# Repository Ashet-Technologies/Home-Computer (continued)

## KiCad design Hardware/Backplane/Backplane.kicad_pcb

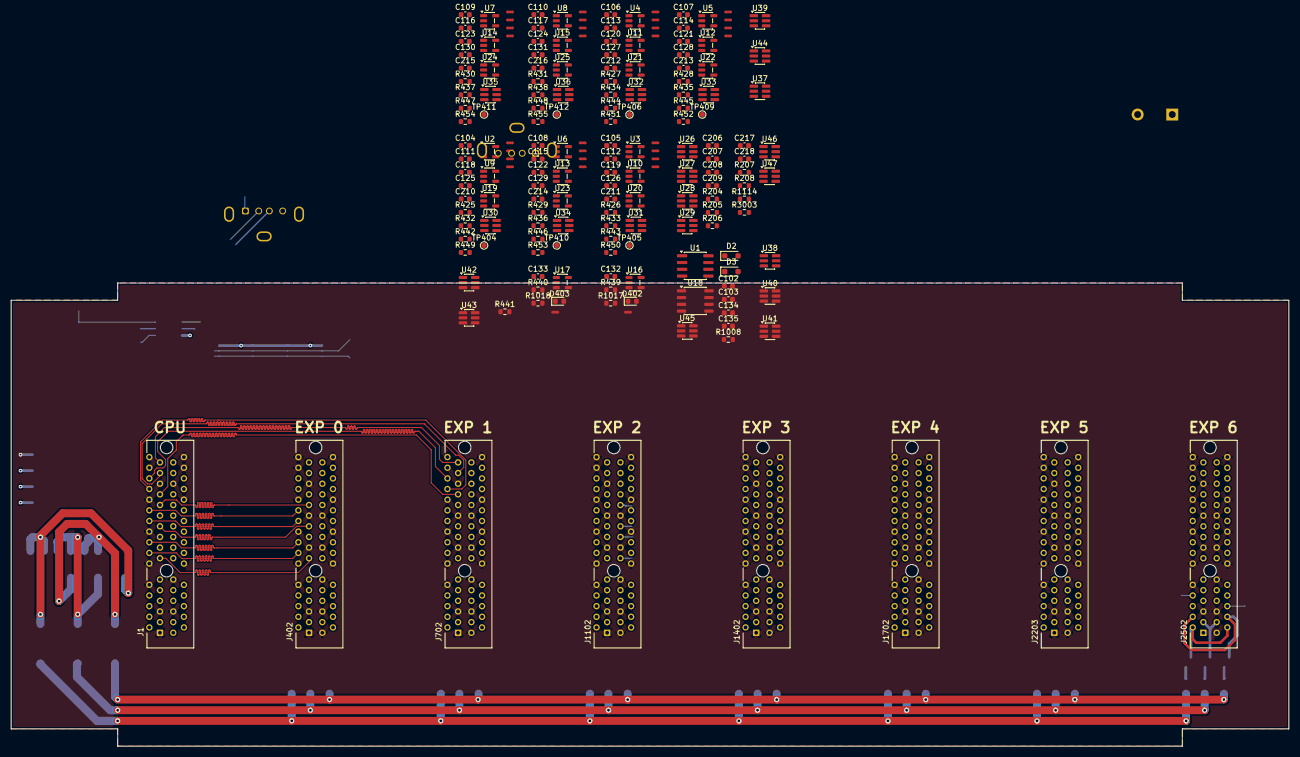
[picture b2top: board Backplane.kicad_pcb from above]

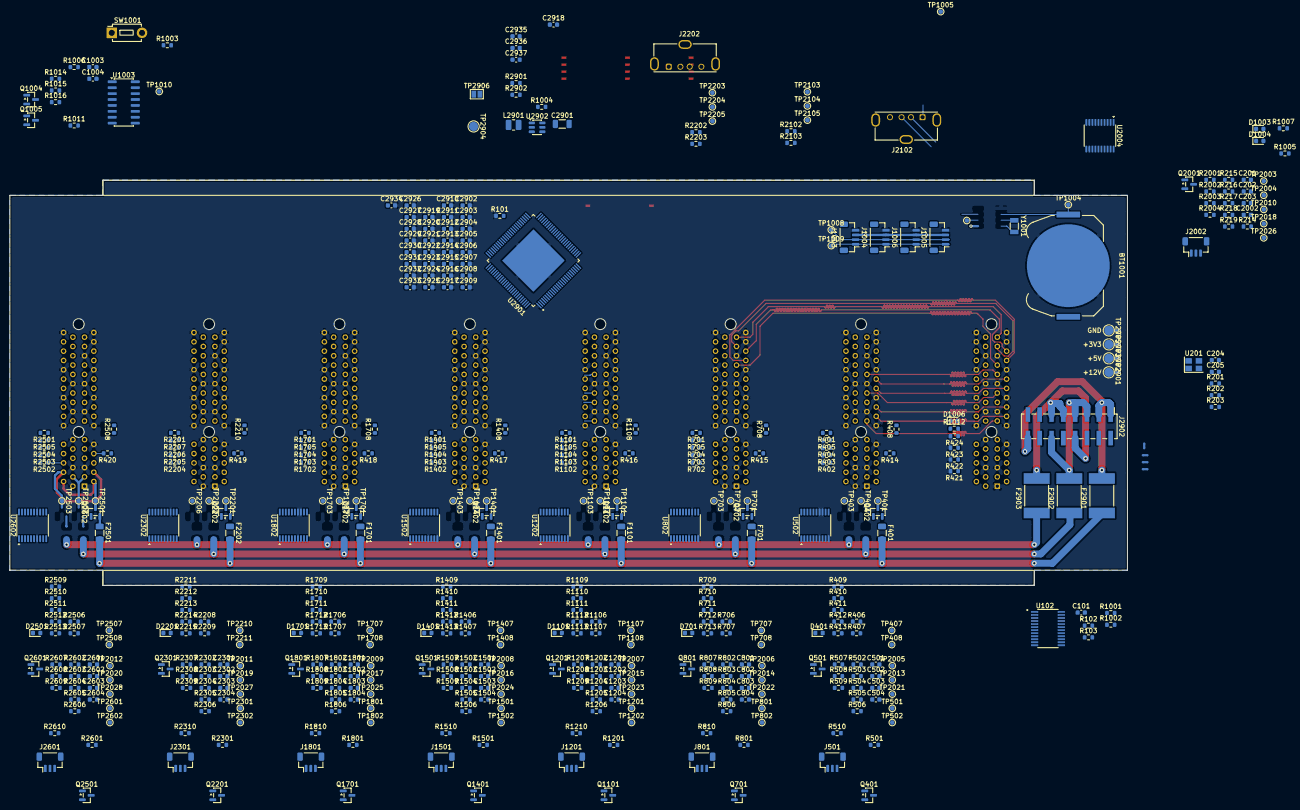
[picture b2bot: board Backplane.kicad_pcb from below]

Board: 4 copper layers, 240.0 x 87.0 mm, 637 parts (453 on the bottom side), 433 nets.

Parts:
BT1001: Keystone 3034; BatteryHolder_Keystone_3034_1x20mm
C101, C102, C103, C104, C105, C106, C107, C108, C109, C110, C111, C112, C113, C114, C115, C116, C117, C118, C119, C120, C121, C122, C123, C124, C125, C126, C127, C128, C129, C130, C131, C132, C133, C134, C135, C201, C202, C203, C204, C206, C207, C208, C209, C210, C211, C212, C213, C214, C215, C216, C217, C218, C501, C502, C503, C504, C801, C802, C803, C804, C1201, C1202, C1203, C1204, C1501, C1502, C1503, C1504, C1801, C1802, C1803, C1804, C2002, C2301, C2302, C2303, C2304, C2601, C2602, C2603, C2604, C2902, C2903, C2904, C2905, C2906, C2907, C2908, C2909, C2910, C2911, C2912, C2913, C2914, C2915, C2916, C2917, C2918, C2919, C2920, C2921, C2922, C2923, C2924, C2925, C2926, C2927, C2928, C2929, C2930, C2931, C2932, C2933, C2934: 100n; C_0603_1608Metric
C205: 10n; C_0603_1608Metric
C1003, C1004: 10u; C_0603_1608Metric
C2901: 220u; C_1206_3216Metric
C2935: 33p; C_0603_1608Metric
C2936, C2937: 22u; C_0603_1608Metric
D2, D3: CUS520,H3F; D_SOD-323_HandSoldering
D401, D402, D403, D701, D1003, D1004, D1006, D1101, D1401, D1701, D2201, D2501: GREEN; LED_0603_1608Metric
F401, F701, F1101, F1401, F1701, F2202, F2501: SMD1206B050TF/15; Fuse_1206_3216Metric
F2901, F2902, F2903: 0ZCF0400FF2A; FUSER_0ZCF0400FF2A
J1, J402, J702, J1102, J1402, J1702, J2203, J2502: 10018784-10201TLF; CONN_10018784-10201TLF
J501, J801, J1201, J1501, J1801, J2002, J2301, J2601: BM03B-SRSS-TB; JST_SH_BM03B-SRSS-TB_1x03-1MP_P1.00mm_Vertical
J1003, J1004, J1005, J1006: BM04B-SRSS-TB; JST_SH_BM04B-SRSS-TB_1x04-1MP_P1.00mm_Vertical
J2102, J2202: Molex 105057; USB_A_Molex_105057_Vertical
J2902: Conn_02x08_Counter_Clockwise; PinHeader_2x08_P2.54mm_Vertical_SMD
L2901: 2.2u; L_1008_2520Metric
NT1, NT2, NT3, NT4, NT5, NT6, NT7, NT8, NT9, NT10, NT11, NT12, NT13, NT14, NT15, NT16, NT17, NT18, NT19, NT20, NT21, NT22, NT23, NT24, NT25, NT26, NT27, NT28, NT29, NT30, NT2904, NT2905, NT2906, NT2907: NetTie_2; NetTie-2_SMD_Pad0.5mm
Q401, Q501, Q701, Q801, Q1004, Q1005, Q1101, Q1201, Q1401, Q1501, Q1701, Q1801, Q2001, Q2201, Q2301, Q2501, Q2601: S3134K; SOT-23
Q402, Q702, Q1102, Q1402, Q1702, Q2202, Q2502: GSF3407; SOT-23
R101, R102, R103, R201, R202, R406, R407, R409, R410, R411, R414, R415, R416, R417, R418, R419, R420, R425, R426, R427, R428, R429, R430, R431, R432, R433, R434, R435, R436, R437, R438, R442, R443, R444, R445, R446, R447, R448, R449, R450, R451, R452, R453, R454, R455, R501, R509, R706, R707, R709, R710, R711, R801, R809, R1001, R1002, R1003, R1004, R1014, R1015, R1016, R1106, R1107, R1109, R1110, R1111, R1114, R1201, R1209, R1406, R1407, R1409, R1410, R1411, R1501, R1509, R1706, R1707, R1709, R1710, R1711, R1801, R1809, R2001, R2003, R2208, R2209, R2211, R2212, R2213, R2301, R2309, R2506, R2507, R2509, R2510, R2511, R2601, R2609: 10K; R_0603_1608Metric
R203, R204, R205, R206, R207, R208, R408, R412, R413, R439, R440, R508, R510, R708, R712, R713, R808, R810, R1005, R1006, R1007, R1008, R1011, R1012, R1017, R1018, R1108, R1112, R1113, R1208, R1210, R1408, R1412, R1413, R1508, R1510, R1708, R1712, R1713, R1808, R1810, R2002, R2004, R2210, R2214, R2215, R2308, R2310, R2508, R2512, R2513, R2608, R2610, R3003: 560; R_0603_1608Metric
R214, R502, R802, R1202, R1502, R1802, R2302, R2602: 6K8 1%; R_0603_1608Metric
R215, R216, R217, R219, R503, R504, R505, R507, R803, R804, R805, R807, R1203, R1204, R1205, R1207, R1503, R1504, R1505, R1507, R1803, R1804, R1805, R1807, R2303, R2304, R2305, R2307, R2603, R2604, R2605, R2607: 1K8 1%; R_0603_1608Metric
R218, R506, R806, R1206, R1506, R1806, R2306, R2606: 560 1%; R_0603_1608Metric
R401, R402, R403, R404, R405, R421, R422, R423, R424, R441, R701, R702, R703, R704, R705, R1101, R1102, R1103, R1104, R1105, R1401, R1402, R1403, R1404, R1405, R1701, R1702, R1703, R1704, R1705, R2102, R2103, R2201, R2202, R2203, R2204, R2205, R2206, R2207, R2501, R2502, R2503, R2504, R2505: 0; R_0603_1608Metric
R2901: 75K 1%; R_0603_1608Metric
R2902: 36K 1%; R_0603_1608Metric
SW1001: Button 12mm; SW_PUSH_1P1T_6x3.5mm_H4.3_APEM_MJTP1243
TP401, TP402, TP403, TP404, TP405, TP406, TP407, TP408, TP409, TP410, TP411, TP412, TP501, TP502, TP701, TP702, TP703, TP707, TP708, TP801, TP802, TP1001, TP1004, TP1005, TP1008, TP1009, TP1010, TP1101, TP1102, TP1103, TP1107, TP1108, TP1201, TP1202, TP1401, TP1402, TP1403, TP1407, TP1408, TP1501, TP1502, TP1701, TP1702, TP1703, TP1707, TP1708, TP1801, TP1802, TP2003, TP2004, TP2005, TP2006, TP2007, TP2008, TP2009, TP2010, TP2011, TP2012, TP2013, TP2014, TP2015, TP2016, TP2017, TP2018, TP2019, TP2020, TP2021, TP2022, TP2023, TP2024, TP2025, TP2026, TP2027, TP2028, TP2103, TP2104, TP2105, TP2201, TP2202, TP2203, TP2204, TP2205, TP2206, TP2210, TP2211, TP2301, TP2302, TP2501, TP2502, TP2503, TP2507, TP2508, TP2601, TP2602: TestPoint_Small; TestPoint_Pad_D1.0mm
TP2901: +12V; TestPoint_Pad_D2.0mm
TP2902: +5V; TestPoint_Pad_D2.0mm
TP2903: +3V3; TestPoint_Pad_D2.0mm
TP2904, TP2905: +1V8; TestPoint_Pad_D2.0mm
TP2906: TestPoint_2Pole; SolderJumper-2_P1.3mm_Open_Pad1.0x1.5mm
U1: 24LC256; SOIC-8_3.9x4.9mm_P1.27mm
U2, U3, U4, U5, U6, U7, U8, U9, U10, U11, U12, U13, U14, U15, U16, U17, U19, U20, U21, U22, U23, U24, U25: TPS2051BDBVR; SOT-23-5
U18: PCF85063AT/AY; SO-8_3.9x4.9mm_P1.27mm
U26, U27, U28, U29, U30, U31, U32, U33, U34, U35, U36, U37, U38, U39, U40, U41, U42, U43, U44, U45, U46, U47: NL7SZ57DBVT1G; SC-74-6_1.55x2.9mm_P0.95mm
U102: TCA9548APWR
U201: OSC48M-3.3I/S3-20T; Crystal_SMD_Abracon_ABM8AIG-4Pin_3.2x2.5mm
U502, U802, U1202, U1502, U1802, U2004, U2302, U2602: CH32V003FxPx; TSSOP-20_4.4x6.5mm_P0.65mm
U1003: CD74HC221M96; SOIC-16_3.9x9.9mm_P1.27mm
U2901: P2X8C4M64P; QFP50P1600X1600X120-101N
U2902: AP3445LW6-7; SOT-23-6
Y1001: 32.768k; Crystal_SMD_3215-2Pin_3.2x1.5mm

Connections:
+1V8: C101.2, C2919.1, C2920.1, C2921.1, C2922.1, C2923.1, C2924.1, C2925.1, C2926.1, C2927.1, C2928.1, C2929.1, C2930.1, C2931.1, C2932.1, C2933.1, C2934.1, R1114.1, R3003.1, TP2904.1 (1_1), TP2906.2 (B), U102.24 (VCC), U2901.2 (VDD), U2901.8 (VDD), U2901.14 (VDD), U2901.20 (VDD), U2901.26 (VDD), U2901.32 (VDD), U2901.38 (VDD), U2901.44 (VDD), U2901.52 (VDD), U2901.58 (VDD), U2901.64 (VDD), U2901.70 (VDD), U2901.76 (VDD), U2901.82 (VDD), U2901.88 (VDD), U2901.94 (VDD)
+3V3: C102.2, C134.2, C135.2, C204.2, C205.2, C206.2, C207.2, C208.2, C209.2, C210.2, C211.2, C212.2, C213.2, C214.2, C215.2, C216.2, C217.2, C218.2, C501.2, C801.2, C1201.2, C1501.2, C1801.2, C2002.2, C2301.2, C2601.2, C2902.1, C2903.1, C2904.1, C2905.1, C2906.1, C2907.1, C2908.1, C2909.1, C2910.1, C2911.1, C2912.1, C2913.1, C2914.1, C2915.1, C2916.1, C2917.1, D3.2 (A), D1006.2 (A), J1.A4 (+3V3), J1.B4 (+3V3), J1003.2, J1004.2, J1005.2, J1006.2, NT2907.2, R102.2, R103.2, R201.2, R203.2, R204.2, R205.2, R206.2, R207.2, R208.2, R218.1, R406.1, R408.1, R432.1, R433.1, R434.1, R435.1, R436.1, R437.1, R438.1, R441.1, R501.2, R510.2, R706.1, R708.1, R801.2, R810.2, R1001.1, R1002.1, R1003.1, R1004.1, R1008.1, R1014.1, R1015.1, R1016.1, R1106.1, R1108.1, R1201.2, R1210.2, R1406.1, R1408.1, R1501.2, R1510.2, R1706.1, R1708.1, R1801.2, R1810.2, R2001.2, R2004.2, R2208.1, R2210.1, R2301.2, R2310.2, R2506.1, R2508.1, R2601.2, R2610.2, TP2903.1 (1_1), U1.8 (VCC), U26.5 (VCC), U27.5 (VCC), U28.5 (VCC), U29.5 (VCC), U30.5 (VCC), U31.5 (VCC), U32.5 (VCC), U33.5 (VCC), U34.5 (VCC), U35.5 (VCC), U36.5 (VCC), U37.5 (VCC), U38.5 (VCC), U39.5 (VCC), U40.5 (VCC), U41.5 (VCC), U42.5 (VCC), U43.5 (VCC), U44.5 (VCC), U45.5 (VCC), U46.5 (VCC), U47.5 (VCC), U201.4 (VDD), U502.9 (VDD), U802.9 (VDD), U1003.16 (VCC), U1202.9 (VDD), U1502.9 (VDD), U1802.9 (VDD), U2004.9 (VDD), U2302.9 (VDD), U2602.9 (VDD), U2901.5 (V0003), U2901.11 (V0407), U2901.17 (V0811), U2901.23 (V1215), U2901.29 (V1619), U2901.35 (V2023), U2901.41 (V2427), U2901.47 (V2831), U2901.55 (V3235), U2901.61 (V3639), U2901.67 (V4043), U2901.73 (V4447), U2901.79 (V4851), U2901.85 (V5255), U2901.91 (V5659), U2901.97 (V6063)
+5V: C2901.2, C2918.2, J1.A3 (+5V), J1.B3 (+5V), NT2906.2, R216.1, TP2902.1 (1_1), U2902.1 (EN), U2902.4 (VIN)
+12V: J1.A2 (+12V), J1.B2 (+12V), NT2905.2, R214.1, TP2901.1 (1_1)
/Builtins/BRD_LED0: R1005.2, U2004.8 (PD0)
/Builtins/BRD_LED1: R1007.2, U2004.19 (PD2)
/Builtins/Management Controller/DAP_SWIO: J2002.3, TP2004.1 (1_1), U2004.18 (PD1)
/Builtins/Management Controller/DAP_~RST: J2002.1, R2001.1, TP2003.1 (1_1), U42.6 (C)
/Builtins/Management Controller/MEAS_+3V3: C203.2, R218.2, R219.1, TP2026.1 (1_1), U2004.3 (PD6)
/Builtins/Management Controller/MEAS_+5V: C202.2, R216.2, R217.1, TP2018.1 (1_1), U2004.2 (PD5)
/Builtins/Management Controller/MEAS_+12V: C201.2, R214.2, R215.1, TP2010.1 (1_1), U2004.1 (PD4)
/Builtins/Management Controller/MGMT_~RST: U42.4 (Y), U2004.4 (PD7)
/Builtins/POWER_OK_{posedge}: U45.1 (B), U1003.5 (2Q)
/Builtins/V_{BAT}: BT1001.1 (+), D2.2 (A), TP1004.1 (1_1)
/Builtins/V_{RTC}: C103.2, D2.1 (K), D3.1 (K), TP1005.1 (1_1), U18.8 (VCC)
/Builtins/~RESET_I2C: R1114.2, U102.3 (~RESET), U2004.20 (PD3)
/Expansions/CLKTREE_{0}: U27.4 (Y), U30.6 (C), U31.6 (C), U32.6 (C)
/Expansions/CLKTREE_{1}: U28.4 (Y), U33.6 (C), U34.6 (C), U35.6 (C)
/Expansions/CLKTREE_{2}: U29.4 (Y), U36.6 (C), U46.1 (B), U47.1 (B)
/Expansions/Clock/CLK_RAW: U26.1 (B), U201.3 (OUT)
/Expansions/Clock/CLK_SPAN: U26.4 (Y), U27.1 (B), U28.1 (B), U29.1 (B)
/Expansions/FAB_~RES: J1.A8 (~FAB_RESET), R101.2, U2901.100 (~RES)
/Expansions/HSTX_{0}: J1.A13 (HSTX0), J402.A13 (HSTX0)
/Expansions/HSTX_{1}: J1.A14 (HSTX1), J402.A14 (HSTX1)
/Expansions/HSTX_{2}: J1.A16 (HSTX2), J402.A16 (HSTX2)
/Expansions/HSTX_{3}: J1.A17 (HSTX3), J402.A17 (HSTX3)
/Expansions/HSTX_{4}: J1.A19 (HSTX4), J402.A19 (HSTX4)
/Expansions/HSTX_{5}: J1.A20 (HSTX5), J402.A20 (HSTX5)
/Expansions/HSTX_{6}: J1.A22 (HSTX6), J402.A22 (HSTX6)
/Expansions/HSTX_{7}: J1.A23 (HSTX7), J402.A23 (HSTX7)
/Expansions/I2C0_{SCL}: J402.A6 (I2C_SCL), R410.2, TP407.1 (1_1), U102.5 (SC0)
/Expansions/I2C0_{SDA}: J402.A7 (I2C_SDA), R409.2, TP408.1 (1_1), U102.4 (SD0)
/Expansions/I2C1_{SCL}: J702.A6 (I2C_SCL), R710.2, TP707.1 (1_1), U102.7 (SC1)
/Expansions/I2C1_{SDA}: J702.A7 (I2C_SDA), R709.2, TP708.1 (1_1), U102.6 (SD1)
/Expansions/I2C2_{SCL}: J1102.A6 (I2C_SCL), R1110.2, TP1107.1 (1_1), U102.9 (SC2)
/Expansions/I2C2_{SDA}: J1102.A7 (I2C_SDA), R1109.2, TP1108.1 (1_1), U102.8 (SD2)
/Expansions/I2C3_{SCL}: J1402.A6 (I2C_SCL), R1410.2, TP1407.1 (1_1), U102.11 (SC3)
/Expansions/I2C3_{SDA}: J1402.A7 (I2C_SDA), R1409.2, TP1408.1 (1_1), U102.10 (SD3)
/Expansions/I2C4_{SCL}: J1702.A6 (I2C_SCL), R1710.2, TP1707.1 (1_1), U102.14 (SC4)
/Expansions/I2C4_{SDA}: J1702.A7 (I2C_SDA), R1709.2, TP1708.1 (1_1), U102.13 (SD4)
/Expansions/I2C5_{SCL}: J2203.A6 (I2C_SCL), R2212.2, TP2210.1 (1_1), U102.16 (SC5)
/Expansions/I2C5_{SDA}: J2203.A7 (I2C_SDA), R2211.2, TP2211.1 (1_1), U102.15 (SD5)
/Expansions/I2C6_{SCL}: J2502.A6 (I2C_SCL), R2510.2, TP2507.1 (1_1), U102.18 (SC6)
/Expansions/I2C6_{SDA}: J2502.A7 (I2C_SDA), R2509.2, TP2508.1 (1_1), U102.17 (SD6)
/Expansions/I2S_{BCLK}: J1.A28 (I2S_BCLK), J702.A28 (I2S_BCLK)
/Expansions/I2S_{LRCLK}: J1.A29 (I2S_WCLK), J702.A29 (I2S_WCLK)
/Expansions/I2S_{MCLK}: J1.A31 (I2S_MCLK), J702.A31 (I2S_MCLK)
/Expansions/I2S_{SDI}: J1.A25 (I2S_SDIN), J702.A25 (I2S_SDIN)
/Expansions/I2S_{SDO}: J1.A26 (I2S_SDOUT), J702.A26 (I2S_SDOUT)
/Expansions/MAIN_CLK: J1.A11 (CLK), U46.4 (Y)
/Expansions/MOD0_{GP0}: J402.B13 (GP0), U2901.3 (P0)
/Expansions/MOD0_{GP1}: J402.B14 (GP1), U2901.4 (P1)
/Expansions/MOD0_{GP2}: J402.B16 (GP2), U2901.6 (P2)
/Expansions/MOD0_{GP3}: J402.B17 (GP3), U2901.7 (P3)
/Expansions/MOD0_{GP4}: J402.B19 (GP4), U2901.9 (P4)
/Expansions/MOD0_{GP5}: J402.B20 (GP5), U2901.10 (P5)
/Expansions/MOD0_{GP6}: J402.B22 (GP6), U2901.12 (P6)
/Expansions/MOD0_{GP7}: J402.B23 (GP7), U2901.13 (P7)
/Expansions/MOD1_{GP0}: J702.B13 (GP0), U2901.15 (P8)
/Expansions/MOD1_{GP1}: J702.B14 (GP1), U2901.16 (P9)
/Expansions/MOD1_{GP2}: J702.B16 (GP2), U2901.18 (P10)
/Expansions/MOD1_{GP3}: J702.B17 (GP3), U2901.19 (P11)
/Expansions/MOD1_{GP4}: J702.B19 (GP4), U2901.21 (P12)
/Expansions/MOD1_{GP5}: J702.B20 (GP5), U2901.22 (P13)
/Expansions/MOD1_{GP6}: J702.B22 (GP6), U2901.24 (P14)
/Expansions/MOD1_{GP7}: J702.B23 (GP7), U2901.25 (P15)
/Expansions/MOD2_{GP0}: J1102.B13 (GP0), U2901.27 (P16)
/Expansions/MOD2_{GP1}: J1102.B14 (GP1), U2901.28 (P17)
/Expansions/MOD2_{GP2}: J1102.B16 (GP2), U2901.30 (P18)
/Expansions/MOD2_{GP3}: J1102.B17 (GP3), U2901.31 (P19)
/Expansions/MOD2_{GP4}: J1102.B19 (GP4), U2901.33 (P20)
/Expansions/MOD2_{GP5}: J1102.B20 (GP5), U2901.34 (P21)
/Expansions/MOD2_{GP6}: J1102.B22 (GP6), U2901.36 (P22)
/Expansions/MOD2_{GP7}: J1102.B23 (GP7), U2901.37 (P23)
/Expansions/MOD3_{GP0}: J1402.B13 (GP0), U2901.39 (P24)
/Expansions/MOD3_{GP1}: J1402.B14 (GP1), U2901.40 (P25)
/Expansions/MOD3_{GP2}: J1402.B16 (GP2), U2901.42 (P26)
/Expansions/MOD3_{GP3}: J1402.B17 (GP3), U2901.43 (P27)
/Expansions/MOD3_{GP4}: J1402.B19 (GP4), U2901.45 (P28)
/Expansions/MOD3_{GP5}: J1402.B20 (GP5), U2901.46 (P29)
/Expansions/MOD3_{GP6}: J1402.B22 (GP6), U2901.48 (P30)
/Expansions/MOD3_{GP7}: J1402.B23 (GP7), U2901.49 (P31)
/Expansions/MOD4_{GP0}: J1702.B13 (GP0), U2901.53 (P32)
/Expansions/MOD4_{GP1}: J1702.B14 (GP1), U2901.54 (P33)
/Expansions/MOD4_{GP2}: J1702.B16 (GP2), U2901.56 (P34)
/Expansions/MOD4_{GP3}: J1702.B17 (GP3), U2901.57 (P35)
/Expansions/MOD4_{GP4}: J1702.B19 (GP4), U2901.59 (P36)
/Expansions/MOD4_{GP5}: J1702.B20 (GP5), U2901.60 (P37)
/Expansions/MOD4_{GP6}: J1702.B22 (GP6), U2901.62 (P38)
/Expansions/MOD4_{GP7}: J1702.B23 (GP7), U2901.63 (P39)
/Expansions/MOD5_{GP0}: J2203.B13 (GP0), U2901.65 (P40)
/Expansions/MOD5_{GP1}: J2203.B14 (GP1), U2901.66 (P41)
/Expansions/MOD5_{GP2}: J2203.B16 (GP2), U2901.68 (P42)
/Expansions/MOD5_{GP3}: J2203.B17 (GP3), U2901.69 (P43)
/Expansions/MOD5_{GP4}: J2203.B19 (GP4), U2901.71 (P44)
/Expansions/MOD5_{GP5}: J2203.B20 (GP5), U2901.72 (P45)
/Expansions/MOD5_{GP6}: J2203.B22 (GP6), U2901.74 (P46)
/Expansions/MOD5_{GP7}: J2203.B23 (GP7), U2901.75 (P47)
/Expansions/MOD6_{GP0}: J2502.B13 (GP0), U2901.77 (P48)
/Expansions/MOD6_{GP1}: J2502.B14 (GP1), U2901.78 (P49)
/Expansions/MOD6_{GP2}: J2502.B16 (GP2), U2901.80 (P50)
/Expansions/MOD6_{GP3}: J2502.B17 (GP3), U2901.81 (P51)
/Expansions/MOD6_{GP4}: J2502.B19 (GP4), U2901.83 (P52)
/Expansions/MOD6_{GP5}: J2502.B20 (GP5), U2901.84 (P53)
/Expansions/MOD6_{GP6}: J2502.B22 (GP6), U2901.86 (P54)
/Expansions/MOD6_{GP7}: J2502.B23 (GP7), U2901.87 (P55)
/Expansions/Module Slot 0/CARD_CLK: J402.A11 (CLK), U30.4 (Y)
/Expansions/Module Slot 0/GATE_POWER_ON: Q401.3 (D), R411.2, R449.2
/Expansions/Module Slot 0/HAS_AUDIO: J402.B6 (~SLOT_AUDIO), R402.1
/Expansions/Module Slot 0/HAS_VIDEO: J402.B7 (~SLOT_HS), R403.1
/Expansions/Module Slot 0/ID_POWER_ON: R442.2, U19.4 (EN), U502.20 (PD3)
/Expansions/Module Slot 0/MOD_+3V3: J402.A4 (+3V3), J402.B4 (+3V3), R409.1, R410.1, R414.1, R506.1, TP403.1 (1_1), U9.1 (OUT)
/Expansions/Module Slot 0/MOD_+3V3_ID: J402.A5 (+3V3_ID), TP404.1 (1_1), U19.1 (OUT)
/Expansions/Module Slot 0/MOD_+5V: J402.A3 (+5V), J402.B3 (+5V), R412.2, R504.1, TP402.1 (1_1), U2.1 (OUT)
/Expansions/Module Slot 0/MOD_+12V: J402.A2 (+12V), J402.B2 (+12V), Q402.3 (D), R502.1, TP401.1 (1_1)
/Expansions/Module Slot 0/MOD_~OC: R432.2, U2.3 (~OC), U9.3 (~OC), U19.3 (~OC), U502.17 (PC7)
/Expansions/Module Slot 0/Management Controller/DAP_SWIO: J501.3, TP502.1 (1_1), U502.18 (PD1)
/Expansions/Module Slot 0/Management Controller/DAP_~RST: J501.1, R501.1, TP501.1 (1_1), U37.6 (C)
/Expansions/Module Slot 0/Management Controller/MEAS_+3V3: C504.2, R506.2, R507.1, TP2021.1 (1_1), U502.3 (PD6)
/Expansions/Module Slot 0/Management Controller/MEAS_+5V: C503.2, R504.2, R505.1, TP2013.1 (1_1), U502.2 (PD5)
/Expansions/Module Slot 0/Management Controller/MEAS_+12V: C502.2, R502.2, R503.1, TP2005.1 (1_1), U502.1 (PD4)
/Expansions/Module Slot 0/Management Controller/MGMT_~RST: U37.4 (Y), U502.4 (PD7)
/Expansions/Module Slot 0/POWER_ON: R407.2, R413.2, U2.4 (EN), U9.4 (EN), U502.8 (PD0)
/Expansions/Module Slot 0/~CARD_RESET: J402.A9 (~RESET), Q501.3 (D)
/Expansions/Module Slot 0/~MOD_CLK_EN: R425.1, U30.1 (B), U502.19 (PD2)
/Expansions/Module Slot 0/~PRESENT: R401.2, R406.2, U502.16 (PC6)
/Expansions/Module Slot 1/CARD_CLK: J702.A11 (CLK), U31.4 (Y)
/Expansions/Module Slot 1/GATE_POWER_ON: Q701.3 (D), R450.2, R711.2
/Expansions/Module Slot 1/HAS_AUDIO: J702.B6 (~SLOT_AUDIO), R702.1
/Expansions/Module Slot 1/HAS_VIDEO: J702.B7 (~SLOT_HS), R703.1
/Expansions/Module Slot 1/ID_POWER_ON: R443.2, U20.4 (EN), U802.20 (PD3)
/Expansions/Module Slot 1/MOD_+3V3: J702.A4 (+3V3), J702.B4 (+3V3), R415.1, R709.1, R710.1, R806.1, TP703.1 (1_1), U10.1 (OUT)
/Expansions/Module Slot 1/MOD_+3V3_ID: J702.A5 (+3V3_ID), TP405.1 (1_1), U20.1 (OUT)
/Expansions/Module Slot 1/MOD_+5V: J702.A3 (+5V), J702.B3 (+5V), R712.2, R804.1, TP702.1 (1_1), U3.1 (OUT)
/Expansions/Module Slot 1/MOD_+12V: J702.A2 (+12V), J702.B2 (+12V), Q702.3 (D), R802.1, TP701.1 (1_1)
/Expansions/Module Slot 1/MOD_~OC: R433.2, U3.3 (~OC), U10.3 (~OC), U20.3 (~OC), U802.17 (PC7)
/Expansions/Module Slot 1/Management Controller/DAP_SWIO: J801.3, TP802.1 (1_1), U802.18 (PD1)
/Expansions/Module Slot 1/Management Controller/DAP_~RST: J801.1, R801.1, TP801.1 (1_1), U38.6 (C)
/Expansions/Module Slot 1/Management Controller/MEAS_+3V3: C804.2, R806.2, R807.1, TP2022.1 (1_1), U802.3 (PD6)
/Expansions/Module Slot 1/Management Controller/MEAS_+5V: C803.2, R804.2, R805.1, TP2014.1 (1_1), U802.2 (PD5)
/Expansions/Module Slot 1/Management Controller/MEAS_+12V: C802.2, R802.2, R803.1, TP2006.1 (1_1), U802.1 (PD4)
/Expansions/Module Slot 1/Management Controller/MGMT_~RST: U38.4 (Y), U802.4 (PD7)
/Expansions/Module Slot 1/POWER_ON: R707.2, R713.2, U3.4 (EN), U10.4 (EN), U802.8 (PD0)
/Expansions/Module Slot 1/~CARD_RESET: J702.A9 (~RESET), Q801.3 (D)
/Expansions/Module Slot 1/~MOD_CLK_EN: R426.1, U31.1 (B), U802.19 (PD2)
/Expansions/Module Slot 1/~PRESENT: R701.2, R706.2, U802.16 (PC6)
/Expansions/Module Slot 2/CARD_CLK: J1102.A11 (CLK), U32.4 (Y)
/Expansions/Module Slot 2/GATE_POWER_ON: Q1101.3 (D), R451.2, R1111.2
/Expansions/Module Slot 2/HAS_AUDIO: J1102.B6 (~SLOT_AUDIO), R1102.1
/Expansions/Module Slot 2/HAS_VIDEO: J1102.B7 (~SLOT_HS), R1103.1
/Expansions/Module Slot 2/ID_POWER_ON: R444.2, U21.4 (EN), U1202.20 (PD3)
/Expansions/Module Slot 2/MOD_+3V3: J1102.A4 (+3V3), J1102.B4 (+3V3), R416.1, R1109.1, R1110.1, R1206.1, TP1103.1 (1_1), U11.1 (OUT)
/Expansions/Module Slot 2/MOD_+3V3_ID: J1102.A5 (+3V3_ID), TP406.1 (1_1), U21.1 (OUT)
/Expansions/Module Slot 2/MOD_+5V: J1102.A3 (+5V), J1102.B3 (+5V), R1112.2, R1204.1, TP1102.1 (1_1), U4.1 (OUT)
/Expansions/Module Slot 2/MOD_+12V: J1102.A2 (+12V), J1102.B2 (+12V), Q1102.3 (D), R1202.1, TP1101.1 (1_1)
/Expansions/Module Slot 2/MOD_~OC: R434.2, U4.3 (~OC), U11.3 (~OC), U21.3 (~OC), U1202.17 (PC7)
/Expansions/Module Slot 2/Management Controller/DAP_SWIO: J1201.3, TP1202.1 (1_1), U1202.18 (PD1)
/Expansions/Module Slot 2/Management Controller/DAP_~RST: J1201.1, R1201.1, TP1201.1 (1_1), U39.6 (C)
/Expansions/Module Slot 2/Management Controller/MEAS_+3V3: C1204.2, R1206.2, R1207.1, TP2023.1 (1_1), U1202.3 (PD6)
/Expansions/Module Slot 2/Management Controller/MEAS_+5V: C1203.2, R1204.2, R1205.1, TP2015.1 (1_1), U1202.2 (PD5)
/Expansions/Module Slot 2/Management Controller/MEAS_+12V: C1202.2, R1202.2, R1203.1, TP2007.1 (1_1), U1202.1 (PD4)
/Expansions/Module Slot 2/Management Controller/MGMT_~RST: U39.4 (Y), U1202.4 (PD7)
/Expansions/Module Slot 2/POWER_ON: R1107.2, R1113.2, U4.4 (EN), U11.4 (EN), U1202.8 (PD0)
/Expansions/Module Slot 2/~CARD_RESET: J1102.A9 (~RESET), Q1201.3 (D)
/Expansions/Module Slot 2/~MOD_CLK_EN: R427.1, U32.1 (B), U1202.19 (PD2)
/Expansions/Module Slot 2/~PRESENT: R1101.2, R1106.2, U1202.16 (PC6)
/Expansions/Module Slot 3/CARD_CLK: J1402.A11 (CLK), U33.4 (Y)
/Expansions/Module Slot 3/GATE_POWER_ON: Q1401.3 (D), R452.2, R1411.2
/Expansions/Module Slot 3/HAS_AUDIO: J1402.B6 (~SLOT_AUDIO), R1402.1
/Expansions/Module Slot 3/HAS_VIDEO: J1402.B7 (~SLOT_HS), R1403.1
/Expansions/Module Slot 3/ID_POWER_ON: R445.2, U22.4 (EN), U1502.20 (PD3)
/Expansions/Module Slot 3/MOD_+3V3: J1402.A4 (+3V3), J1402.B4 (+3V3), R417.1, R1409.1, R1410.1, R1506.1, TP1403.1 (1_1), U12.1 (OUT)
/Expansions/Module Slot 3/MOD_+3V3_ID: J1402.A5 (+3V3_ID), TP409.1 (1_1), U22.1 (OUT)
/Expansions/Module Slot 3/MOD_+5V: J1402.A3 (+5V), J1402.B3 (+5V), R1412.2, R1504.1, TP1402.1 (1_1), U5.1 (OUT)
/Expansions/Module Slot 3/MOD_+12V: J1402.A2 (+12V), J1402.B2 (+12V), Q1402.3 (D), R1502.1, TP1401.1 (1_1)
/Expansions/Module Slot 3/MOD_~OC: R435.2, U5.3 (~OC), U12.3 (~OC), U22.3 (~OC), U1502.17 (PC7)
/Expansions/Module Slot 3/Management Controller/DAP_SWIO: J1501.3, TP1502.1 (1_1), U1502.18 (PD1)
/Expansions/Module Slot 3/Management Controller/DAP_~RST: J1501.1, R1501.1, TP1501.1 (1_1), U40.6 (C)
/Expansions/Module Slot 3/Management Controller/MEAS_+3V3: C1504.2, R1506.2, R1507.1, TP2024.1 (1_1), U1502.3 (PD6)
/Expansions/Module Slot 3/Management Controller/MEAS_+5V: C1503.2, R1504.2, R1505.1, TP2016.1 (1_1), U1502.2 (PD5)
/Expansions/Module Slot 3/Management Controller/MEAS_+12V: C1502.2, R1502.2, R1503.1, TP2008.1 (1_1), U1502.1 (PD4)
/Expansions/Module Slot 3/Management Controller/MGMT_~RST: U40.4 (Y), U1502.4 (PD7)
/Expansions/Module Slot 3/POWER_ON: R1407.2, R1413.2, U5.4 (EN), U12.4 (EN), U1502.8 (PD0)
/Expansions/Module Slot 3/~CARD_RESET: J1402.A9 (~RESET), Q1501.3 (D)
/Expansions/Module Slot 3/~MOD_CLK_EN: R428.1, U33.1 (B), U1502.19 (PD2)
/Expansions/Module Slot 3/~PRESENT: R1401.2, R1406.2, U1502.16 (PC6)
/Expansions/Module Slot 4/CARD_CLK: J1702.A11 (CLK), U34.4 (Y)
/Expansions/Module Slot 4/GATE_POWER_ON: Q1701.3 (D), R453.2, R1711.2
/Expansions/Module Slot 4/HAS_AUDIO: J1702.B6 (~SLOT_AUDIO), R1702.1
/Expansions/Module Slot 4/HAS_VIDEO: J1702.B7 (~SLOT_HS), R1703.1
/Expansions/Module Slot 4/ID_POWER_ON: R446.2, U23.4 (EN), U1802.20 (PD3)
/Expansions/Module Slot 4/MOD_+3V3: J1702.A4 (+3V3), J1702.B4 (+3V3), R418.1, R1709.1, R1710.1, R1806.1, TP1703.1 (1_1), U13.1 (OUT)
/Expansions/Module Slot 4/MOD_+3V3_ID: J1702.A5 (+3V3_ID), TP410.1 (1_1), U23.1 (OUT)
/Expansions/Module Slot 4/MOD_+5V: J1702.A3 (+5V), J1702.B3 (+5V), R1712.2, R1804.1, TP1702.1 (1_1), U6.1 (OUT)
/Expansions/Module Slot 4/MOD_+12V: J1702.A2 (+12V), J1702.B2 (+12V), Q1702.3 (D), R1802.1, TP1701.1 (1_1)
/Expansions/Module Slot 4/MOD_~OC: R436.2, U6.3 (~OC), U13.3 (~OC), U23.3 (~OC), U1802.17 (PC7)
/Expansions/Module Slot 4/Management Controller/DAP_SWIO: J1801.3, TP1802.1 (1_1), U1802.18 (PD1)
/Expansions/Module Slot 4/Management Controller/DAP_~RST: J1801.1, R1801.1, TP1801.1 (1_1), U41.6 (C)
/Expansions/Module Slot 4/Management Controller/MEAS_+3V3: C1804.2, R1806.2, R1807.1, TP2025.1 (1_1), U1802.3 (PD6)
/Expansions/Module Slot 4/Management Controller/MEAS_+5V: C1803.2, R1804.2, R1805.1, TP2017.1 (1_1), U1802.2 (PD5)
/Expansions/Module Slot 4/Management Controller/MEAS_+12V: C1802.2, R1802.2, R1803.1, TP2009.1 (1_1), U1802.1 (PD4)
/Expansions/Module Slot 4/Management Controller/MGMT_~RST: U41.4 (Y), U1802.4 (PD7)
/Expansions/Module Slot 4/POWER_ON: R1707.2, R1713.2, U6.4 (EN), U13.4 (EN), U1802.8 (PD0)
/Expansions/Module Slot 4/~CARD_RESET: J1702.A9 (~RESET), Q1801.3 (D)
/Expansions/Module Slot 4/~MOD_CLK_EN: R429.1, U34.1 (B), U1802.19 (PD2)
/Expansions/Module Slot 4/~PRESENT: R1701.2, R1706.2, U1802.16 (PC6)
/Expansions/Module Slot 5/CARD_CLK: J2203.A11 (CLK), U35.4 (Y)
/Expansions/Module Slot 5/GATE_POWER_ON: Q2201.3 (D), R454.2, R2213.2
/Expansions/Module Slot 5/HAS_AUDIO: J2203.B6 (~SLOT_AUDIO), R2204.1
/Expansions/Module Slot 5/HAS_VIDEO: J2203.B7 (~SLOT_HS), R2205.1
/Expansions/Module Slot 5/ID_POWER_ON: R447.2, U24.4 (EN), U2302.20 (PD3)
/Expansions/Module Slot 5/MOD_+3V3: J2203.A4 (+3V3), J2203.B4 (+3V3), R419.1, R2211.1, R2212.1, R2306.1, TP2206.1 (1_1), U14.1 (OUT)
/Expansions/Module Slot 5/MOD_+3V3_ID: J2203.A5 (+3V3_ID), TP411.1 (1_1), U24.1 (OUT)
/Expansions/Module Slot 5/MOD_+5V: J2203.A3 (+5V), J2203.B3 (+5V), R2214.2, R2304.1, TP2202.1 (1_1), U7.1 (OUT)
/Expansions/Module Slot 5/MOD_+12V: J2203.A2 (+12V), J2203.B2 (+12V), Q2202.3 (D), R2302.1, TP2201.1 (1_1)
/Expansions/Module Slot 5/MOD_~OC: R437.2, U7.3 (~OC), U14.3 (~OC), U24.3 (~OC), U2302.17 (PC7)
/Expansions/Module Slot 5/Management Controller/DAP_SWIO: J2301.3, TP2302.1 (1_1), U2302.18 (PD1)
/Expansions/Module Slot 5/Management Controller/DAP_~RST: J2301.1, R2301.1, TP2301.1 (1_1), U43.6 (C)
/Expansions/Module Slot 5/Management Controller/MEAS_+3V3: C2304.2, R2306.2, R2307.1, TP2027.1 (1_1), U2302.3 (PD6)
/Expansions/Module Slot 5/Management Controller/MEAS_+5V: C2303.2, R2304.2, R2305.1, TP2019.1 (1_1), U2302.2 (PD5)
/Expansions/Module Slot 5/Management Controller/MEAS_+12V: C2302.2, R2302.2, R2303.1, TP2011.1 (1_1), U2302.1 (PD4)
/Expansions/Module Slot 5/Management Controller/MGMT_~RST: U43.4 (Y), U2302.4 (PD7)
/Expansions/Module Slot 5/POWER_ON: R2209.2, R2215.2, U7.4 (EN), U14.4 (EN), U2302.8 (PD0)
/Expansions/Module Slot 5/~CARD_RESET: J2203.A9 (~RESET), Q2301.3 (D)
/Expansions/Module Slot 5/~MOD_CLK_EN: R430.1, U35.1 (B), U2302.19 (PD2)
/Expansions/Module Slot 5/~PRESENT: R2201.2, R2208.2, U2302.16 (PC6)
/Expansions/Module Slot 6/CARD_CLK: J2502.A11 (CLK), U36.4 (Y)
/Expansions/Module Slot 6/GATE_POWER_ON: Q2501.3 (D), R455.2, R2511.2
/Expansions/Module Slot 6/HAS_AUDIO: J2502.B6 (~SLOT_AUDIO), R2502.1
/Expansions/Module Slot 6/HAS_VIDEO: J2502.B7 (~SLOT_HS), R2503.1
/Expansions/Module Slot 6/ID_POWER_ON: R448.2, U25.4 (EN), U2602.20 (PD3)
/Expansions/Module Slot 6/MOD_+3V3: J2502.A4 (+3V3), J2502.B4 (+3V3), R420.1, R2509.1, R2510.1, R2606.1, TP2503.1 (1_1), U15.1 (OUT)
/Expansions/Module Slot 6/MOD_+3V3_ID: J2502.A5 (+3V3_ID), TP412.1 (1_1), U25.1 (OUT)
/Expansions/Module Slot 6/MOD_+5V: J2502.A3 (+5V), J2502.B3 (+5V), R2512.2, R2604.1, TP2502.1 (1_1), U8.1 (OUT)
/Expansions/Module Slot 6/MOD_+12V: J2502.A2 (+12V), J2502.B2 (+12V), Q2502.3 (D), R2602.1, TP2501.1 (1_1)
/Expansions/Module Slot 6/MOD_~OC: R438.2, U8.3 (~OC), U15.3 (~OC), U25.3 (~OC), U2602.17 (PC7)
/Expansions/Module Slot 6/Management Controller/DAP_SWIO: J2601.3, TP2602.1 (1_1), U2602.18 (PD1)
/Expansions/Module Slot 6/Management Controller/DAP_~RST: J2601.1, R2601.1, TP2601.1 (1_1), U44.6 (C)
/Expansions/Module Slot 6/Management Controller/MEAS_+3V3: C2604.2, R2606.2, R2607.1, TP2028.1 (1_1), U2602.3 (PD6)
/Expansions/Module Slot 6/Management Controller/MEAS_+5V: C2603.2, R2604.2, R2605.1, TP2020.1 (1_1), U2602.2 (PD5)
/Expansions/Module Slot 6/Management Controller/MEAS_+12V: C2602.2, R2602.2, R2603.1, TP2012.1 (1_1), U2602.1 (PD4)
/Expansions/Module Slot 6/Management Controller/MGMT_~RST: U44.4 (Y), U2602.4 (PD7)
/Expansions/Module Slot 6/POWER_ON: R2507.2, R2513.2, U8.4 (EN), U15.4 (EN), U2602.8 (PD0)
/Expansions/Module Slot 6/~CARD_RESET: J2502.A9 (~RESET), Q2601.3 (D)
/Expansions/Module Slot 6/~MOD_CLK_EN: R431.1, U36.1 (B), U2602.19 (PD2)
/Expansions/Module Slot 6/~PRESENT: R2501.2, R2506.2, U2602.16 (PC6)
/Expansions/P2_CLK: U47.4 (Y), U2901.51 (XI)
/FAB0: J1.B13 (GP0), U2901.89 (P56)
/FAB1: J1.B14 (GP1), U2901.90 (P57)
/FAB2: J1.B16 (GP2), U2901.92 (P58)
/FAB3: J1.B17 (GP3), U2901.93 (P59)
/FAB4: J1.B19 (GP4), U2901.95 (P60)
/FAB5: J1.B20 (GP5), U2901.96 (P61)
/FAB6: J1.B22 (GP6), U2901.98 (P62)
/FAB7: J1.B23 (GP7), U2901.99 (P63)
/I2C^{FAB}_{SCL}: J1.A6 (I2C_SCL), R103.1, U102.22 (SCL)
/I2C^{FAB}_{SDA}: J1.A7 (I2C_SDA), R102.1, U102.23 (SDA)
/USB A Socket 1/VBUS: J2102.1 (VBUS), TP2103.1 (1_1), U16.1 (OUT)
/USB A Socket 1/VBUS_UNFUSED: C132.2, NT22.2, R439.2, R1017.2, U16.5 (IN)
/USB A Socket 2/VBUS: J2202.1 (VBUS), TP2203.1 (1_1), U17.1 (OUT)
/USB A Socket 2/VBUS_UNFUSED: C133.2, NT23.2, R440.2, R1018.2, U17.5 (IN)
/USB_{0}_D+: J1.B25 (USB0_D+), J2102.3 (D+), TP2104.1 (1_1)
/USB_{0}_D-: J1.B26 (USB0_D-), J2102.2 (D-), TP2105.1 (1_1)
/USB_{1}_D+: J1.B28 (USB1_D+), J2202.3 (D+), TP2204.1 (1_1)
/USB_{1}_D-: J1.B29 (USB1_D-), J2202.2 (D-), TP2205.1 (1_1)
GND: BT1001.2 (-), C101.1, C102.1, C103.1, C104.1, C105.1, C106.1, C107.1, C108.1, C109.1, C110.1, C111.1, C112.1, C113.1, C114.1, C115.1, C116.1, C117.1, C118.1, C119.1, C120.1, C121.1, C122.1, C123.1, C124.1, C132.1, C133.1, C134.1, C135.1, C201.1, C202.1, C203.1, C204.1, C205.1, C206.1, C207.1, C208.1, C209.1, C210.1, C211.1, C212.1, C213.1, C214.1, C215.1, C216.1, C217.1, C218.1, C501.1, C502.1, C503.1, C504.1, C801.1, C802.1, C803.1, C804.1, C1201.1, C1202.1, C1203.1, C1204.1, C1501.1, C1502.1, C1503.1, C1504.1, C1801.1, C1802.1, C1803.1, C1804.1, C2002.1, C2301.1, C2302.1, C2303.1, C2304.1, C2601.1, C2602.1, C2603.1, C2604.1, C2901.1, C2902.2, C2903.2, C2904.2, C2905.2, C2906.2, C2907.2, C2908.2, C2909.2, C2910.2, C2911.2, C2912.2, C2913.2, C2914.2, C2915.2, C2916.2, C2917.2, C2918.1, C2919.2, C2920.2, C2921.2, C2922.2, C2923.2, C2924.2, C2925.2, C2926.2, C2927.2, C2928.2, C2929.2, C2930.2, C2931.2, C2932.2, C2933.2, C2934.2, C2936.1, C2937.1, D401.1 (K), D701.1 (K), D1003.1 (K), D1004.1 (K), D1101.1 (K), D1401.1 (K), D1701.1 (K), D2201.1 (K), D2501.1 (K), J1.A1 (GND), J1.A10 (GND), J1.A12 (GND), J1.A15 (GND), J1.A18 (GND), J1.A21 (GND), J1.A24 (GND), J1.A27 (GND), J1.A30 (GND), J1.A32 (GND), J1.B1 (GND), J1.B5 (GND), J1.B11 (GND), J1.B12 (GND), J1.B15 (GND), J1.B18 (GND), J1.B21 (GND), J1.B24 (GND), J1.B27 (GND), J1.B30 (GND), J1.B32 (GND), J402.A1 (GND), J402.A10 (GND), J402.A12 (GND), J402.A15 (GND), J402.A18 (GND), J402.A21 (GND), J402.A24 (GND), J402.A27 (GND), J402.A30 (GND), J402.A32 (GND), J402.B1 (GND), J402.B5 (GND), J402.B11 (GND), J402.B12 (GND), J402.B15 (GND), J402.B18 (GND), J402.B21 (GND), J402.B24 (GND), J402.B32 (GND), J501.2, J702.A1 (GND), J702.A10 (GND), J702.A12 (GND), J702.A15 (GND), J702.A18 (GND), J702.A21 (GND), J702.A24 (GND), J702.A27 (GND), J702.A30 (GND), J702.A32 (GND), J702.B1 (GND), J702.B5 (GND), J702.B11 (GND), J702.B12 (GND), J702.B15 (GND), J702.B18 (GND), J702.B21 (GND), J702.B24 (GND), J702.B32 (GND), J801.2, J1003.1, J1004.1, J1005.1, J1006.1, J1102.A1 (GND), J1102.A10 (GND), J1102.A12 (GND), J1102.A15 (GND), J1102.A18 (GND), J1102.A21 (GND), J1102.A24 (GND), J1102.A27 (GND), J1102.A30 (GND), J1102.A32 (GND), J1102.B1 (GND), J1102.B5 (GND), J1102.B11 (GND), J1102.B12 (GND), J1102.B15 (GND), J1102.B18 (GND), J1102.B21 (GND), J1102.B24 (GND), J1102.B32 (GND), J1201.2, J1402.A1 (GND), J1402.A10 (GND), J1402.A12 (GND), J1402.A15 (GND), J1402.A18 (GND), J1402.A21 (GND), J1402.A24 (GND), J1402.A27 (GND), J1402.A30 (GND), J1402.A32 (GND), J1402.B1 (GND), J1402.B5 (GND), J1402.B11 (GND), J1402.B12 (GND), J1402.B15 (GND), J1402.B18 (GND), J1402.B21 (GND), J1402.B24 (GND), J1402.B32 (GND), J1501.2, J1702.A1 (GND), J1702.A10 (GND), J1702.A12 (GND), J1702.A15 (GND), J1702.A18 (GND), J1702.A21 (GND), J1702.A24 (GND), J1702.A27 (GND), J1702.A30 (GND), J1702.A32 (GND), J1702.B1 (GND), J1702.B5 (GND), J1702.B11 (GND), J1702.B12 (GND), J1702.B15 (GND), J1702.B18 (GND), J1702.B21 (GND), J1702.B24 (GND), J1702.B32 (GND), J1801.2, J2002.2, J2102.4 (GND), J2202.4 (GND), J2203.A1 (GND), J2203.A10 (GND), J2203.A12 (GND), J2203.A15 (GND), J2203.A18 (GND), J2203.A21 (GND), J2203.A24 (GND), J2203.A27 (GND), J2203.A30 (GND), J2203.A32 (GND), J2203.B1 (GND), J2203.B5 (GND), J2203.B11 (GND), J2203.B12 (GND), J2203.B15 (GND), J2203.B18 (GND), J2203.B21 (GND), J2203.B24 (GND), J2203.B32 (GND), J2301.2, J2502.A1 (GND), J2502.A10 (GND), J2502.A12 (GND), J2502.A15 (GND), J2502.A18 (GND), J2502.A21 (GND), J2502.A24 (GND), J2502.A27 (GND), J2502.A30 (GND), J2502.A32 (GND), J2502.B1 (GND), J2502.B5 (GND), J2502.B11 (GND), J2502.B12 (GND), J2502.B15 (GND), J2502.B18 (GND), J2502.B21 (GND), J2502.B24 (GND), J2502.B32 (GND), J2601.2, NT2904.2, Q401.2 (S), Q501.2 (S), Q701.2 (S), Q801.2 (S), Q1004.2 (S), Q1005.2 (S), Q1101.2 (S), Q1201.2 (S), Q1401.2 (S), Q1501.2 (S), Q1701.2 (S), Q1801.2 (S), Q2001.2 (S), Q2201.2 (S), Q2301.2 (S), Q2501.2 (S), Q2601.2 (S), R101.1, R202.1, R215.2, R217.2, R219.2, R402.2, R403.2, R404.2, R405.2, R407.1, R421.2, R422.2, R423.2, R424.2, R425.2, R426.2, R427.2, R428.2, R429.2, R430.2, R431.2, R442.1, R443.1, R444.1, R445.1, R446.1, R447.1, R448.1, R503.2, R505.2, R507.2, R509.1, R702.2, R703.2, R704.2, R705.2, R707.1, R803.2, R805.2, R807.2, R809.1, R1102.2, R1103.2, R1104.2, R1105.2, R1107.1, R1203.2, R1205.2, R1207.2, R1209.1, R1402.2, R1403.2, R1404.2, R1405.2, R1407.1, R1503.2, R1505.2, R1507.2, R1509.1, R1702.2, R1703.2, R1704.2, R1705.2, R1707.1, R1803.2, R1805.2, R1807.2, R1809.1, R2003.1, R2102.1, R2103.1, R2202.1, R2203.1, R2204.2, R2205.2, R2206.2, R2207.2, R2209.1, R2303.2, R2305.2, R2307.2, R2309.1, R2502.2, R2503.2, R2504.2, R2505.2, R2507.1, R2603.2, R2605.2, R2607.2, R2609.1, R2902.1, SW1001.1, TP2905.1 (1_1), U1.4 (GND), U1.7 (WP), U2.2 (GND), U3.2 (GND), U4.2 (GND), U5.2 (GND), U6.2 (GND), U7.2 (GND), U8.2 (GND), U9.2 (GND), U10.2 (GND), U11.2 (GND), U12.2 (GND), U13.2 (GND), U14.2 (GND), U15.2 (GND), U16.2 (GND), U17.2 (GND), U18.4 (VSS), U19.2 (GND), U20.2 (GND), U21.2 (GND), U22.2 (GND), U23.2 (GND), U24.2 (GND), U25.2 (GND), U26.2 (GND), U26.3 (A), U27.2 (GND), U27.3 (A), U28.2 (GND), U28.3 (A), U29.2 (GND), U29.3 (A), U30.2 (GND), U31.2 (GND), U32.2 (GND), U33.2 (GND), U34.2 (GND), U35.2 (GND), U36.2 (GND), U37.2 (GND), U38.2 (GND), U39.2 (GND), U40.2 (GND), U41.2 (GND), U42.2 (GND), U43.2 (GND), U44.2 (GND), U45.2 (GND), U46.2 (GND), U46.3 (A), U47.2 (GND), U47.3 (A), U102.12 (GND), U201.2 (GND), U502.7 (VSS), U502.10 (PC0), U502.13 (PC3), U502.14 (PC4), U802.7 (VSS), U802.13 (PC3), U802.14 (PC4), U1003.8 (GND), U1003.9 (~2A), U1202.7 (VSS), U1202.10 (PC0), U1202.14 (PC4), U1502.7 (VSS), U1502.14 (PC4), U1802.7 (VSS), U1802.10 (PC0), U1802.13 (PC3), U2004.7 (VSS), U2302.7 (VSS), U2302.13 (PC3), U2602.7 (VSS), U2602.10 (PC0), U2901.1 (TEST), U2901.101 (GND), U2902.2 (GND)
I2C^{BRD}_{SCL}: J1003.4, J1004.4, J1005.4, J1006.4, R1001.2, TP1009.1 (1_1), U1.6 (SCL), U18.6 (SCL), U102.20 (SC7), U502.12 (PC2), U802.12 (PC2), U1202.12 (PC2), U1502.12 (PC2), U1802.12 (PC2), U2004.12 (PC2), U2302.12 (PC2), U2602.12 (PC2)
I2C^{BRD}_{SDA}: J1003.3, J1004.3, J1005.3, J1006.3, R1002.2, TP1008.1 (1_1), U1.5 (SDA), U18.5 (SDA), U102.19 (SD7), U502.11 (PC1), U802.11 (PC1), U1202.11 (PC1), U1502.11 (PC1), U1802.11 (PC1), U2004.11 (PC1), U2302.11 (PC1), U2602.11 (PC1)
MAIN_+3V3: F2903.1, NT8.1, NT9.1, NT10.1, NT11.1, NT12.1, NT13.1, NT14.1, NT24.1, NT25.1, NT26.1, NT27.1, NT28.1, NT29.1, NT30.1, NT2907.1
MAIN_+5V: F2902.1, NT1.1, NT2.1, NT3.1, NT4.1, NT5.1, NT6.1, NT7.1, NT22.1, NT23.1, NT2906.1
MAIN_+12V: F2901.1, NT15.1, NT16.1, NT17.1, NT18.1, NT19.1, NT20.1, NT21.1, NT2905.1
MAIN_GND: J2902.2, J2902.4, J2902.6, J2902.8, J2902.10, J2902.12, J2902.14, J2902.16, NT2904.1
unnamed: D401.2 (A), R412.1
unnamed: D402.2 (A), R439.1
unnamed: D402.1 (K), U16.3 (~OC)
unnamed: D403.2 (A), R440.1
unnamed: D403.1 (K), U17.3 (~OC)
unnamed: D701.2 (A), R712.1
unnamed: D1003.2 (A), R1005.1
unnamed: D1004.2 (A), R1007.1
unnamed: D1006.1 (K), R1012.1
unnamed: D1101.2 (A), R1112.1
unnamed: D1401.2 (A), R1412.1
unnamed: D1701.2 (A), R1712.1
unnamed: D2201.2 (A), R2214.1
unnamed: D2501.2 (A), R2512.1
unnamed: F401.2, NT15.2, R411.1
unnamed: F701.2, NT16.2, R711.1
unnamed: F1101.2, NT17.2, R1111.1
unnamed: F1401.2, NT18.2, R1411.1
unnamed: F1701.2, NT19.2, R1711.1
unnamed: F2202.2, NT20.2, R2213.1
unnamed: F2501.2, NT21.2, R2511.1
unnamed: J1.A5 (+3V3_ID), R441.2
unnamed: J1.B10 (~PRESENT), R1012.2
unnamed: J1.B6 (~SLOT_AUDIO), R421.1
unnamed: J1.B7 (~SLOT_HS), R422.1
unnamed: J1.B8 (~SLOT_USB0), R423.1
unnamed: J1.B9 (~SLOT_USB1), R424.1
unnamed: J402.A8 (+3V3_10K), R414.2
unnamed: J402.B10 (~PRESENT), R401.1
unnamed: J402.B8 (~SLOT_FUNC0), R404.1
unnamed: J402.B9 (~SLOT_FUNC1), R405.1
unnamed: J702.A8 (+3V3_10K), R415.2
unnamed: J702.B10 (~PRESENT), R701.1
unnamed: J702.B8 (~SLOT_FUNC0), R704.1
unnamed: J702.B9 (~SLOT_FUNC1), R705.1
unnamed: J1102.A8 (+3V3_10K), R416.2
unnamed: J1102.B10 (~PRESENT), R1101.1
unnamed: J1102.B8 (~SLOT_FUNC0), R1104.1
unnamed: J1102.B9 (~SLOT_FUNC1), R1105.1
unnamed: J1402.A8 (+3V3_10K), R417.2
unnamed: J1402.B10 (~PRESENT), R1401.1
unnamed: J1402.B8 (~SLOT_FUNC0), R1404.1
unnamed: J1402.B9 (~SLOT_FUNC1), R1405.1
unnamed: J1702.A8 (+3V3_10K), R418.2
unnamed: J1702.B10 (~PRESENT), R1701.1
unnamed: J1702.B8 (~SLOT_FUNC0), R1704.1
unnamed: J1702.B9 (~SLOT_FUNC1), R1705.1
unnamed: R2102.2, R2103.2
unnamed: R2202.2, R2203.2
unnamed: J2203.A8 (+3V3_10K), R419.2
unnamed: J2203.B10 (~PRESENT), R2201.1
unnamed: J2203.B8 (~SLOT_FUNC0), R2206.1
unnamed: J2203.B9 (~SLOT_FUNC1), R2207.1
unnamed: J2502.A8 (+3V3_10K), R420.2
unnamed: J2502.B10 (~PRESENT), R2501.1
unnamed: J2502.B8 (~SLOT_FUNC0), R2504.1
unnamed: J2502.B9 (~SLOT_FUNC1), R2505.1
unnamed: F2901.2, J2902.1, J2902.3
unnamed: F2902.2, J2902.5, J2902.7
unnamed: F2903.2, J2902.9, J2902.11
unnamed: Q401.1 (G), R413.1
unnamed: C125.1, Q402.1 (G), R449.1
unnamed: C125.2, F401.1, Q402.2 (S)
unnamed: Q501.1 (G), R508.2
unnamed: Q701.1 (G), R713.1
unnamed: C126.1, Q702.1 (G), R450.1
unnamed: C126.2, F701.1, Q702.2 (S)
unnamed: Q801.1 (G), R808.2
unnamed: Q1004.1 (G), R1011.1
unnamed: Q1005.1 (G), R1006.1
unnamed: Q1101.1 (G), R1113.1
unnamed: C127.1, Q1102.1 (G), R451.1
unnamed: C127.2, F1101.1, Q1102.2 (S)
unnamed: Q1201.1 (G), R1208.2
unnamed: Q1401.1 (G), R1413.1
unnamed: C128.1, Q1402.1 (G), R452.1
unnamed: C128.2, F1401.1, Q1402.2 (S)
unnamed: Q1501.1 (G), R1508.2
unnamed: Q1701.1 (G), R1713.1
unnamed: C129.1, Q1702.1 (G), R453.1
unnamed: C129.2, F1701.1, Q1702.2 (S)
unnamed: Q1801.1 (G), R1808.2
unnamed: Q2001.1 (G), R2002.2
unnamed: Q2201.1 (G), R2215.1
unnamed: C130.1, Q2202.1 (G), R454.1
unnamed: C130.2, F2202.1, Q2202.2 (S)
unnamed: Q2301.1 (G), R2308.2
unnamed: Q2501.1 (G), R2513.1
unnamed: C131.1, Q2502.1 (G), R455.1
unnamed: C131.2, F2501.1, Q2502.2 (S)
unnamed: Q2601.1 (G), R2608.2
unnamed: C2935.2, C2936.2, C2937.2, L2901.2, R2901.2, TP2906.1 (A)
unnamed: R1008.2, U1.1 (A0), U1.2 (A1), U1.3 (A2)
unnamed: C111.2, NT1.2, U2.5 (IN)
unnamed: C112.2, NT2.2, U3.5 (IN)
unnamed: C113.2, NT3.2, U4.5 (IN)
unnamed: C114.2, NT4.2, U5.5 (IN)
unnamed: C115.2, NT5.2, U6.5 (IN)
unnamed: C116.2, NT6.2, U7.5 (IN)
unnamed: C117.2, NT7.2, U8.5 (IN)
unnamed: C118.2, NT8.2, U9.5 (IN)
unnamed: C119.2, NT9.2, U10.5 (IN)
unnamed: C120.2, NT10.2, U11.5 (IN)
unnamed: C121.2, NT11.2, U12.5 (IN)
unnamed: C122.2, NT12.2, U13.5 (IN)
unnamed: C123.2, NT13.2, U14.5 (IN)
unnamed: C124.2, NT14.2, U15.5 (IN)
unnamed: R1017.1, U16.4 (EN)
unnamed: R1018.1, U17.4 (EN)
unnamed: TP1001.1 (1_1), U18.7 (CLKOUT)
unnamed: U18.1 (OSCI), Y1001.2
unnamed: U18.2 (OSCO), Y1001.1
unnamed: C104.2, NT24.2, U19.5 (IN)
unnamed: C105.2, NT25.2, U20.5 (IN)
unnamed: C106.2, NT26.2, U21.5 (IN)
unnamed: C107.2, NT27.2, U22.5 (IN)
unnamed: C108.2, NT28.2, U23.5 (IN)
unnamed: C109.2, NT29.2, U24.5 (IN)
unnamed: C110.2, NT30.2, U25.5 (IN)
unnamed: R203.1, U26.6 (C)
unnamed: R204.1, U27.6 (C)
unnamed: R205.1, U28.6 (C)
unnamed: R206.1, U29.6 (C)
unnamed: R408.2, U30.3 (A)
unnamed: R708.2, U31.3 (A)
unnamed: R1108.2, U32.3 (A)
unnamed: R1408.2, U33.3 (A)
unnamed: R1708.2, U34.3 (A)
unnamed: R2210.2, U35.3 (A)
unnamed: R2508.2, U36.3 (A)
unnamed: R510.1, U37.3 (A)
unnamed: R810.1, U38.3 (A)
unnamed: R1210.1, U39.3 (A)
unnamed: R1510.1, U40.3 (A)
unnamed: R1810.1, U41.3 (A)
unnamed: R2004.1, U42.3 (A)
unnamed: R2310.1, U43.3 (A)
unnamed: R2610.1, U44.3 (A)
unnamed: R1011.2, U45.4 (Y)
unnamed: R207.1, U46.6 (C)
unnamed: R208.1, U47.6 (C)
unnamed: R3003.2, U102.1 (A0), U102.2 (A1), U102.21 (A2)
unnamed: R201.1, R202.2, U201.1 (E/D)
unnamed: R508.1, R509.2, U502.15 (PC5)
unnamed: R808.1, R809.2, U802.15 (PC5)
unnamed: R1016.2, U1003.2 (1B), U1003.3 (~1R), U1003.11 (~2R)
unnamed: C1003.2, U1003.14 (1C_{X})
unnamed: C1003.1, R1014.2, U1003.15 (1C_{X}R_{X})
unnamed: R1006.2, U1003.13 (1Q)
unnamed: C1004.2, U1003.6 (2C_{X})
unnamed: C1004.1, R1015.2, U1003.7 (2C_{X}R_{X})
unnamed: R1208.1, R1209.2, U1202.15 (PC5)
unnamed: R1508.1, R1509.2, U1502.15 (PC5)
unnamed: R1808.1, R1809.2, U1802.15 (PC5)
unnamed: R2002.1, R2003.2, U2004.15 (PC5)
unnamed: R2308.1, R2309.2, U2302.15 (PC5)
unnamed: R2608.1, R2609.2, U2602.15 (PC5)
unnamed: C2935.1, R2901.1, R2902.2, U2902.6 (FB)
unnamed: L2901.1, U2902.3 (LX)
POWER_OK: J2902.15, R1004.2, U45.3 (A), U45.6 (C), U1003.10 (2B), U2902.5 (PG)
~RESET: J1.A9 (~RESET), Q1004.3 (D), Q1005.3 (D), Q2001.3 (D), R1003.2, SW1001.2, TP1010.1 (1_1), U37.1 (B), U38.1 (B), U39.1 (B), U40.1 (B), U41.1 (B), U42.1 (B), U43.1 (B), U44.1 (B), U1003.1 (~1A)
